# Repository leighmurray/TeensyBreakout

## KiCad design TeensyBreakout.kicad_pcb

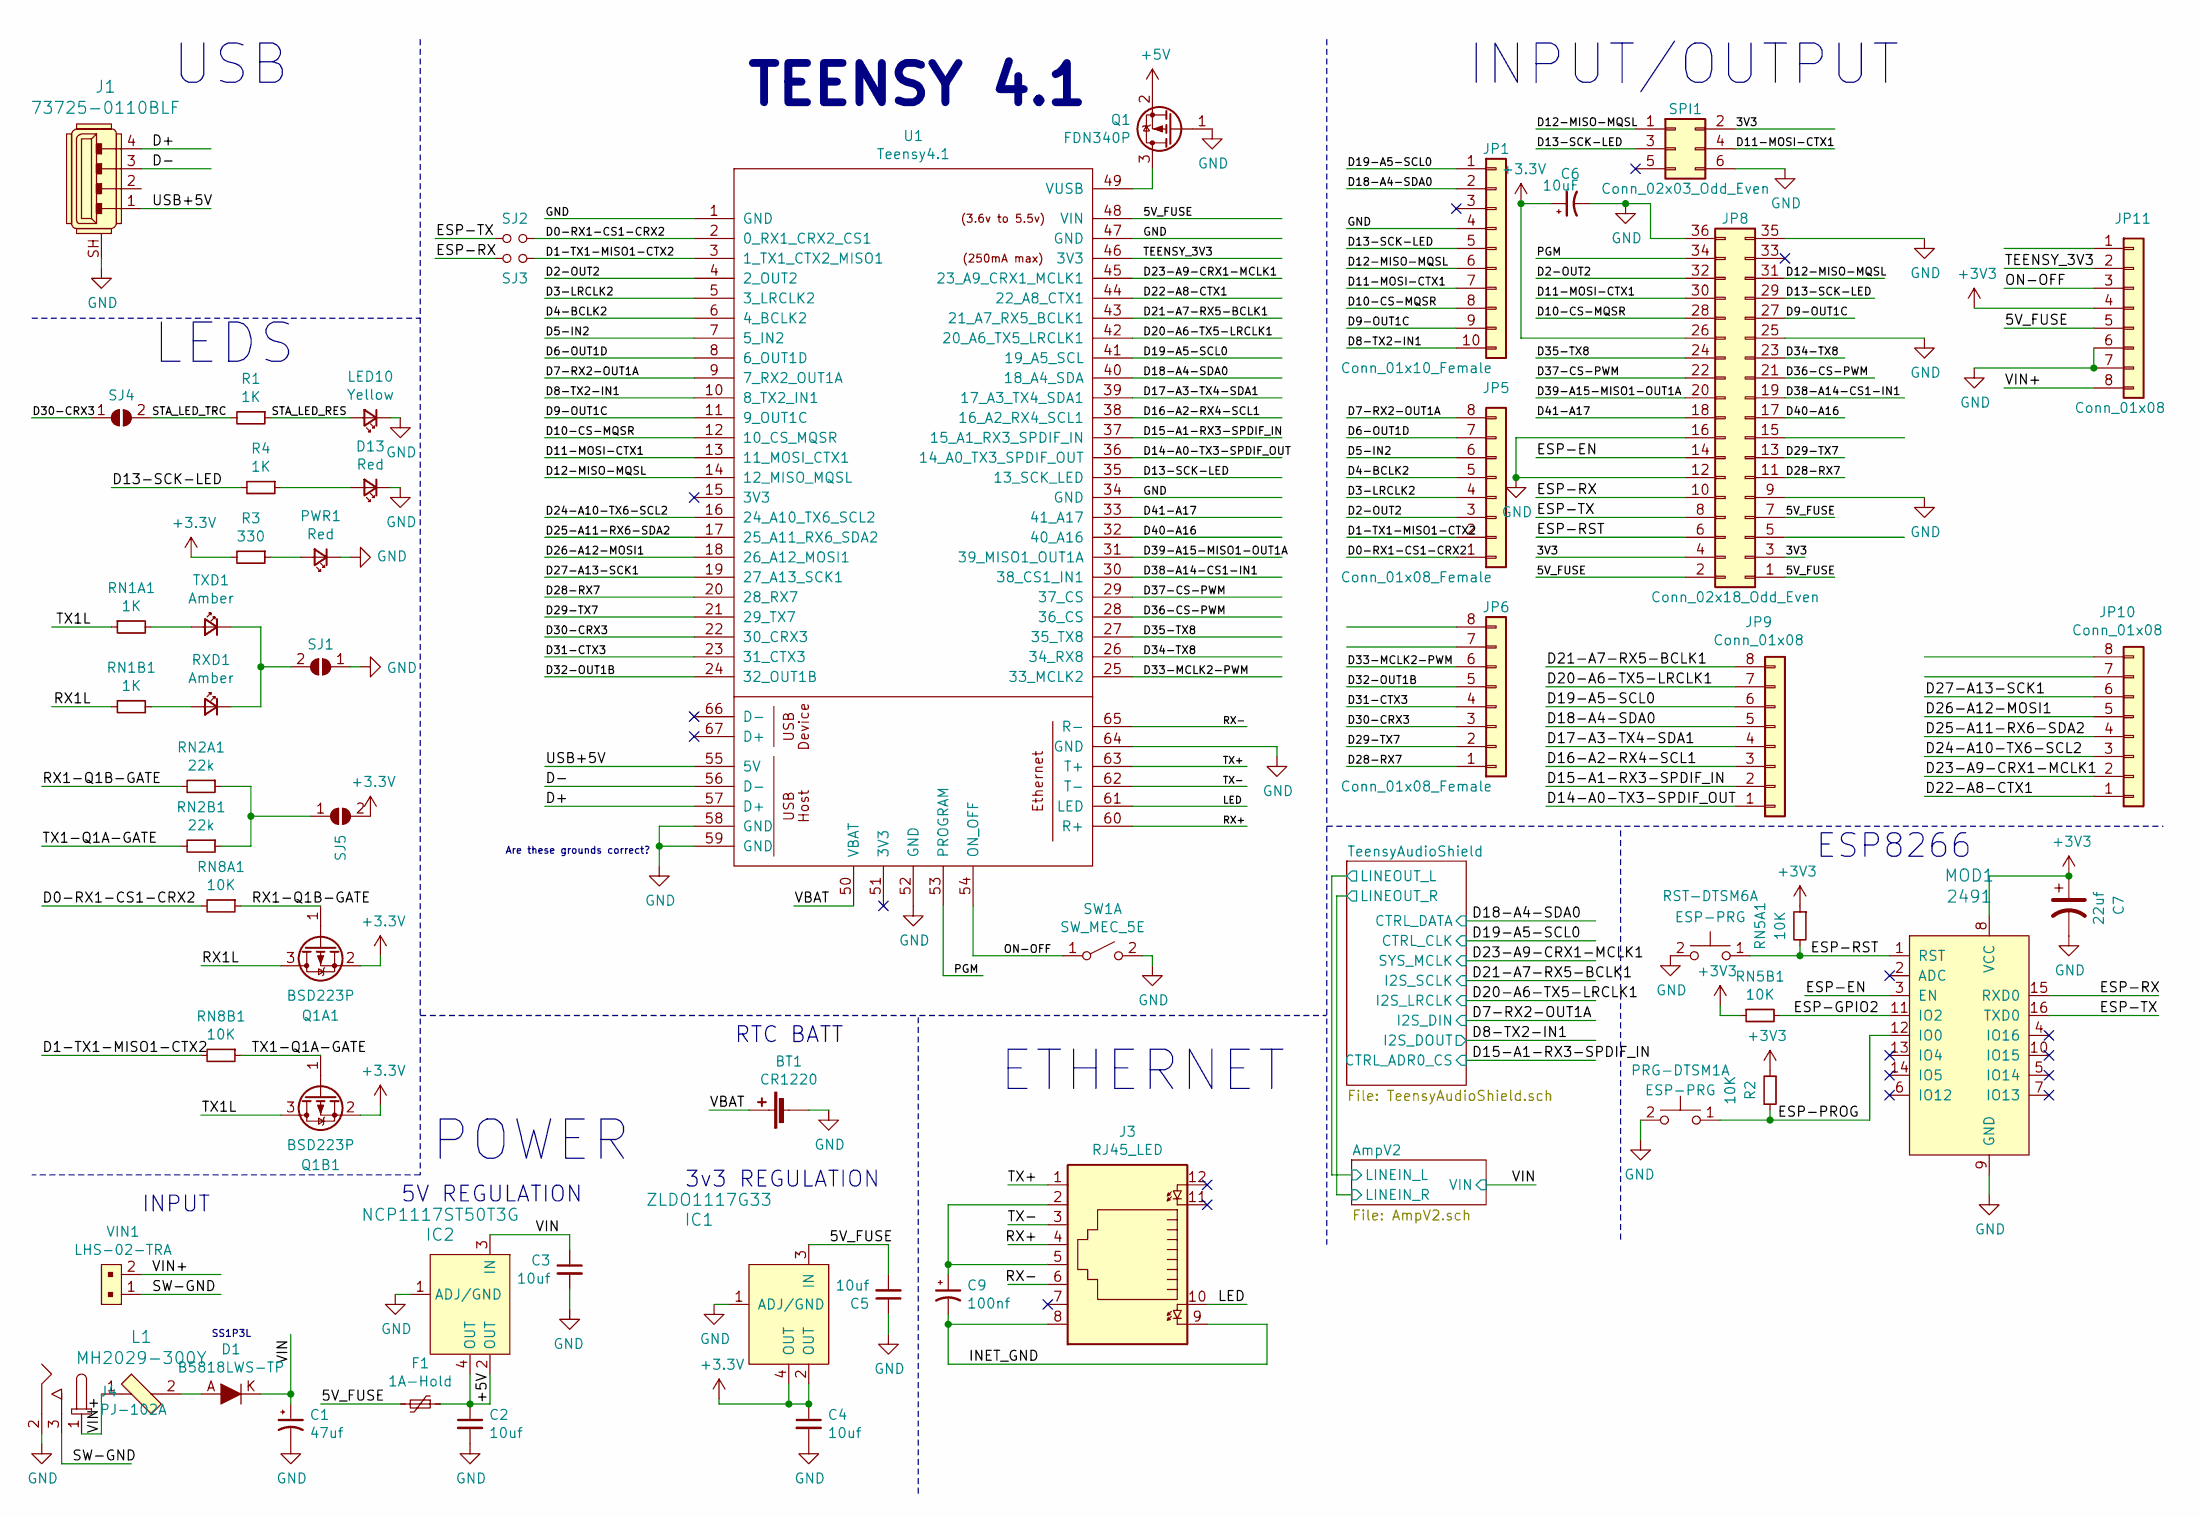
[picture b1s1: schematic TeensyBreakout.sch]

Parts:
BT1: CR1220; BatteryHolder_Keystone_3000_1x12mm
C1: 47uf; CP_Radial_D5.0mm_P2.50mm
C2, C3, C4, C5: 10uf; C_0603_1608Metric_Pad1.08x0.95mm_HandSolder
C6: 10uF; C_0603_1608Metric_Pad1.08x0.95mm_HandSolder
C7: 22uf; C_0603_1608Metric_Pad1.08x0.95mm_HandSolder
C9: 100nf; C_0603_1608Metric_Pad1.08x0.95mm_HandSolder
D1: B5818LWS-TP; SOD-323
D13: Red; LED_0603_1608Metric_Pad1.05x0.95mm_HandSolder
F1: 1A-Hold; Fuse_0603_1608Metric_Pad1.05x0.95mm_HandSolder
IC1: ZLDO1117G33; SOT-223; MPN NCP1117ST33T3G; Digi-Key_PN NCP1117ST33T3GOSCT-ND
IC2: NCP1117ST50T3G; SOT-223; MPN NCP1117ST50T3G; Digi-Key_PN NCP1117ST50T3GOSCT-ND
J1: 73725-0110BLF; USB_A_Female_Vertical_RA_73725-0110BLF; MPN 73725-0110BLF; Digi-Key_PN 609-1041-ND
J3: RJ45_LED; RJ45_Amphenol_RJHSE538X
J4: PJ-102A; Barrel_Jack_5.5mmODx2.1mmID_PJ-102A; MPN PJ-102A; Digi-Key_PN CP-102A-ND
JP1: Conn_01x10_Female; PinSocket_1x10_P2.54mm_Vertical
JP5, JP6: Conn_01x08_Female; PinSocket_1x08_P2.54mm_Vertical
JP8: Conn_02x18_Odd_Even; PinSocket_2x18_P2.54mm_VerticalFlipped
JP9, JP10, JP11: Conn_01x08; PinSocket_1x08_P2.54mm_Vertical
L1: MH2029-300Y; R_0603_1608Metric_Pad0.98x0.95mm_HandSolder; MPN BLM18PG121SN1D; Digi-Key_PN 490-1037-1-ND
LED10: Yellow; LED_0603_1608Metric_Pad1.05x0.95mm_HandSolder
MOD1: 2491; WIFI_Module_ESP8266_2491; MPN 2491; Digi-Key_PN 1528-1438-ND
PRG-DTSM1: ESP-PRG; SW_PUSH_6mm
PWR1: Red; LED_0603_1608Metric_Pad1.05x0.95mm_HandSolder
Q1: FDN340P; SOT-23
Q1A1, Q1B1: BSD223P; SOT-23
R1, R4: 1K; R_0603_1608Metric_Pad0.98x0.95mm_HandSolder
R2: 10K; R_0603_1608Metric_Pad0.98x0.95mm_HandSolder
R3: 330; R_0603_1608Metric_Pad0.98x0.95mm_HandSolder
RN1A1, RN1B1: 1K; R_0603_1608Metric_Pad0.98x0.95mm_HandSolder
RN2A1, RN2B1: 22k; R_0603_1608Metric_Pad0.98x0.95mm_HandSolder
RN5A1, RN5B1, RN8A1, RN8B1: 10K; R_0603_1608Metric_Pad0.98x0.95mm_HandSolder
RST-DTSM6: ESP-PRG; SW_PUSH_6mm
RXD1: Amber; LED_0603_1608Metric_Pad1.05x0.95mm_HandSolder
SJ1, SJ4, SJ5: SolderJumper_2_Open; SolderJumper-2_P1.3mm_Open_TrianglePad1.0x1.5mm
SJ2, SJ3: Jumper_NO_Small; PinHeader_1x02_P2.54mm_Vertical
SPI1: Conn_02x03_Odd_Even; PinSocket_2x03_P2.54mm_Vertical(Flipped)
SW1: SW_MEC_5E; SW_PUSH_6mm
TXD1: Amber; LED_0603_1608Metric_Pad1.05x0.95mm_HandSolder
U1: Teensy4.1; Teensy41
VIN1: LHS-02-TRA; JST_PH_S2B-PH-K_1x02_P2.00mm_Horizontal; MPN M20-9990246; Digi-Key_PN 952-2262-ND

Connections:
+5V: C2.1, F1.1, IC2.2 (OUT), IC2.4 (OUT), Q1.2 (S)
/3V3: JP8.3, JP8.4, SPI1.2
/5V_FUSE: C5.2, F1.2, IC1.3 (IN), JP8.1, JP8.2, JP8.7, JP11.5, U1.48 (VIN)
/D0-RX1-CS1-CRX2: JP5.1, RN8A1.2, SJ2.2, U1.2 (0_RX1_CRX2_CS1)
/D1-TX1-MISO1-CTX2: JP5.2, RN8B1.2, SJ3.2, U1.3 (1_TX1_CTX2_MISO1)
/D2-OUT2: JP5.3, JP8.32, U1.4 (2_OUT2)
/D3-LRCLK2: JP5.4, U1.5 (3_LRCLK2)
/D4-BCLK2: JP5.5, U1.6 (4_BCLK2)
/D5-IN2: JP5.6, U1.7 (5_IN2)
/D6-OUT1D: JP5.7, U1.8 (6_OUT1D)
/D7-RX2-OUT1A: JP5.8, U1.9 (7_RX2_OUT1A); also elsewhere on the board
/D8-TX2-IN1: JP1.10, U1.10 (8_TX2_IN1); also elsewhere on the board
/D9-OUT1C: JP1.9, JP8.27, U1.11 (9_OUT1C)
/D10-CS-MQSR: JP1.8, JP8.28, U1.12 (10_CS_MQSR)
/D11-MOSI-CTX1: JP1.7, JP8.30, SPI1.4, U1.13 (11_MOSI_CTX1)
/D12-MISO-MQSL: JP1.6, JP8.31, SPI1.1, U1.14 (12_MISO_MQSL)
/D13-SCK-LED: JP1.5, JP8.29, R4.2, SPI1.3, U1.35 (13_SCK_LED)
/D14-A0-TX3-SPDIF_OUT: JP9.1, U1.36 (14_A0_TX3_SPDIF_OUT)
/D15-A1-RX3-SPDIF_IN: JP9.2, U1.37 (15_A1_RX3_SPDIF_IN); also elsewhere on the board
/D16-A2-RX4-SCL1: JP9.3, U1.38 (16_A2_RX4_SCL1)
/D17-A3-TX4-SDA1: JP9.4, U1.39 (17_A3_TX4_SDA1)
/D18-A4-SDA0: JP1.2, JP9.5, U1.40 (18_A4_SDA); also elsewhere on the board
/D19-A5-SCL0: JP1.1, JP9.6, U1.41 (19_A5_SCL); also elsewhere on the board
/D20-A6-TX5-LRCLK1: JP9.7, U1.42 (20_A6_TX5_LRCLK1); also elsewhere on the board
/D21-A7-RX5-BCLK1: JP9.8, U1.43 (21_A7_RX5_BCLK1); also elsewhere on the board
/D22-A8-CTX1: JP10.1, U1.44 (22_A8_CTX1)
/D23-A9-CRX1-MCLK1: JP10.2, U1.45 (23_A9_CRX1_MCLK1); also elsewhere on the board
/D24-A10-TX6-SCL2: JP10.3, U1.16 (24_A10_TX6_SCL2)
/D25-A11-RX6-SDA2: JP10.4, U1.17 (25_A11_RX6_SDA2)
/D26-A12-MOSI1: JP10.5, U1.18 (26_A12_MOSI1)
/D27-A13-SCK1: JP10.6, U1.19 (27_A13_SCK1)
/D28-RX7: JP6.1, JP8.11, U1.20 (28_RX7)
/D29-TX7: JP6.2, JP8.13, U1.21 (29_TX7)
/D30-CRX3: JP6.3, SJ4.1 (A), U1.22 (30_CRX3)
/D31-CTX3: JP6.4, U1.23 (31_CTX3)
/D32-OUT1B: JP6.5, U1.24 (32_OUT1B)
/D33-MCLK2-PWM: JP6.6, U1.25 (33_MCLK2)
/D34-TX8: JP8.23, U1.26 (34_RX8)
/D35-TX8: JP8.24, U1.27 (35_TX8)
/D36-CS-PWM: JP8.21, U1.28 (36_CS)
/D37-CS-PWM: JP8.22, U1.29 (37_CS)
/D38-A14-CS1-IN1: JP8.19, U1.30 (38_CS1_IN1)
/D39-A15-MISO1-OUT1A: JP8.20, U1.31 (39_MISO1_OUT1A)
/D40-A16: JP8.17, U1.32 (40_A16)
/D41-A17: JP8.18, U1.33 (41_A17)
/D+: J1.4, U1.57 (D+)
/D-: J1.3, U1.56 (D-)
/ESP-EN: JP8.14, MOD1.3 (EN)
/ESP-GPIO2: MOD1.11 (IO2), RN5B1.2
/ESP-PROG: MOD1.12 (IO0), PRG-DTSM1.1 (C), R2.2
/ESP-RST: JP8.6, MOD1.1 (RST), RN5A1.2, RST-DTSM6.1 (C)
/ESP-RX: JP8.10, MOD1.15 (RXD0), SJ3.1
/ESP-TX: JP8.8, MOD1.16 (TXD0), SJ2.1
/INET_GND: C9.2, J3.8, J3.9
/LED: J3.10, U1.61 (LED)
/ON-OFF: JP11.3, SW1.1 (A), U1.54 (ON_OFF)
/PGM: JP8.34, U1.53 (PROGRAM)
/RX1-Q1B-GATE: Q1A1.1 (G), RN2A1.2, RN8A1.1
/RX1L: Q1A1.3 (D), RN1B1.1
/RX+: J3.4, U1.60 (R+)
/RX-: J3.6, U1.65 (R-)
/STA_LED_RES: LED10.2 (A), R1.1
/STA_LED_TRC: R1.2, SJ4.2 (B)
/SW-GND: J4.3, VIN1.1
/TEENSY_3V3: JP11.2, U1.46 (3V3)
/TX1-Q1A-GATE: Q1B1.1 (G), RN2B1.2, RN8B1.1
/TX1L: Q1B1.3 (D), RN1A1.1
/TX+: J3.1, U1.63 (T+)
/TX-: J3.3, U1.62 (T-)
/USB+5V: J1.1, U1.55 (5V)
/VBAT: BT1.1 (+), U1.50 (VBAT)
/VIN: C1.1, C3.1, D1.K, IC2.3 (IN); also elsewhere on the board
/VIN+: J4.1, JP11.8, L1.1, VIN1.2
GND: BT1.2 (-), C1.2, C2.2, C3.2, C4.2, C5.1, C6.2, C7.2, D13.1 (K), IC1.1 (ADJ/GND), IC2.1 (ADJ/GND), J1.SH, J4.2, JP1.4, JP8.9, JP8.12, JP8.16, JP8.25, JP8.35, JP8.36, JP11.6, JP11.7, LED10.1 (K), MOD1.9 (GND), PRG-DTSM1.2 (D), PWR1.1 (K), Q1.1 (G), RST-DTSM6.2 (D), SJ1.1 (A), SPI1.6, SW1.2 (B), U1.1 (GND), U1.34 (GND), U1.47 (GND), U1.52 (GND), U1.58 (GND), U1.59 (GND), U1.64 (GND); also elsewhere on the board
unnamed: C9.1, J3.2, J3.5
unnamed: D1.A, L1.2
unnamed: D13.2 (A), R4.1
unnamed: PWR1.2 (A), R3.1
unnamed: Q1.3 (D), U1.49 (VUSB)
unnamed: RN1A1.2, TXD1.2 (A)
unnamed: RN1B1.2, RXD1.2 (A)
unnamed: RN2A1.1, RN2B1.1, SJ5.1 (A)
unnamed: RXD1.1 (K), SJ1.2 (B), TXD1.1 (K)

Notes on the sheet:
TEENSY 4.1
INPUT/OUTPUT
USB
LEDS
POWER
3v3 REGULATION
RTC BATT
5V REGULATION
INPUT
ETHERNET
Are these grounds correct?
SS1P3L
ESP8266

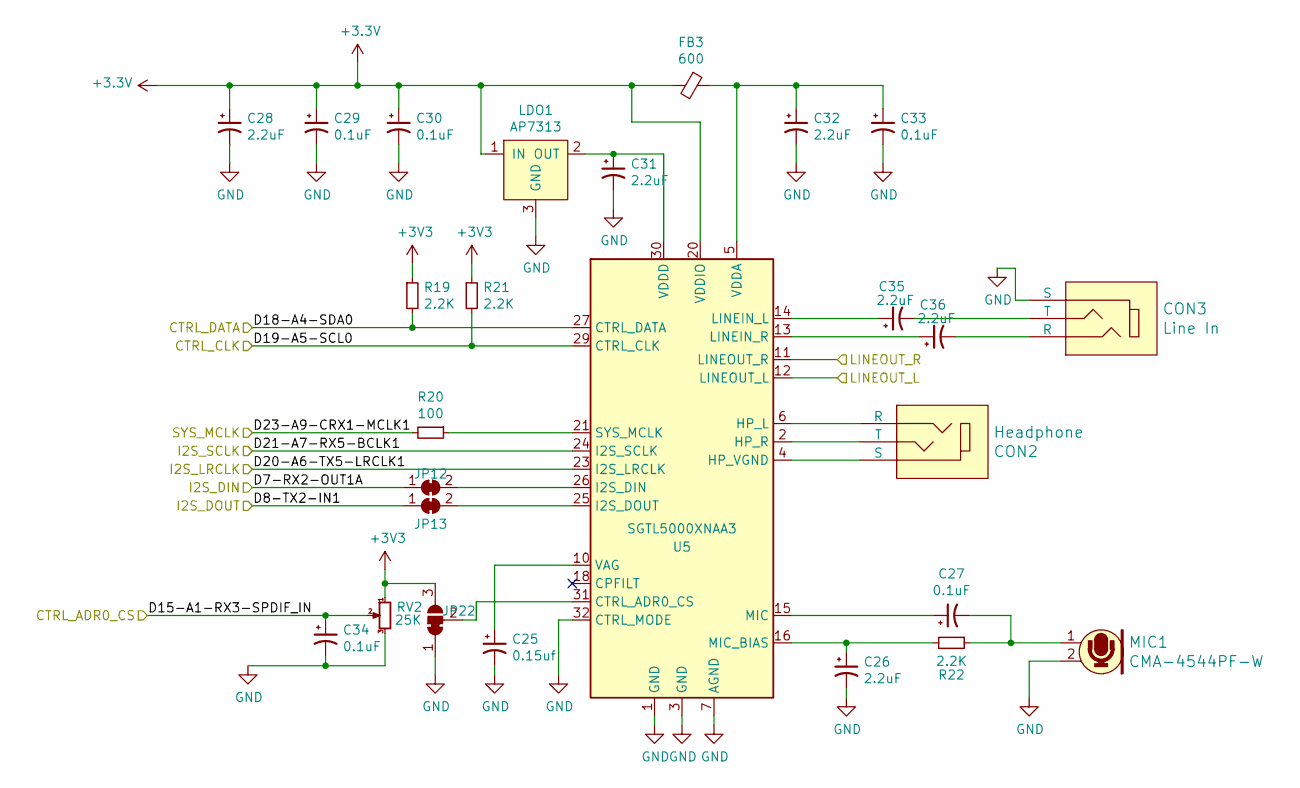
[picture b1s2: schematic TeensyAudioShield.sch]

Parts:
C25: 0.15uf; C_0603_1608Metric_Pad1.08x0.95mm_HandSolder
C26, C28, C31, C32, C35, C36: 2.2uF; C_0603_1608Metric_Pad1.08x0.95mm_HandSolder
C27, C29, C30, C33, C34: 0.1uF; C_0603_1608Metric_Pad1.08x0.95mm_HandSolder
CON2: Headphone; Switch_Slide_11.6x4mm_SJ-3523-SMT; MPN SJ-3523-SMT-TR; Digi-Key_PN CP-3523SJCT-ND
CON3: Line In; Switch_Slide_11.6x4mm_SJ-3523-SMT; MPN SJ-3523-SMT-TR; Digi-Key_PN CP-3523SJCT-ND
FB3: 600; 0805
JP12, JP13: SolderJumper_2_Bridged; SolderJumper-2_P1.3mm_Bridged_Pad1.0x1.5mm
JP22: SolderJumper_3_Bridged12; SolderJumper-3_P1.3mm_Bridged12_RoundedPad1.0x1.5mm_NumberL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
LDO1: AP7313; SOT-23_Handsoldering
MIC1: CMA-4544PF-W; Mic_CMA-4544PF-W; MPN CMA-4544PF-W; Digi-Key_PN 102-1721-ND
R19, R21, R22: 2.2K; R_0603_1608Metric_Pad0.98x0.95mm_HandSolder
R20: 100; R_0603_1608Metric_Pad0.98x0.95mm_HandSolder
RV2: 25K; Potentiometer_TT_P0915N
U5: SGTL5000XNAA3; QFN-32-1EP_5x5mm_P0.5mm_EP3.6x3.6mm

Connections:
/AmpV2/LINEIN_L: U5.12 (LINEOUT_L); also elsewhere on the board
/AmpV2/LINEIN_R: U5.11 (LINEOUT_R); also elsewhere on the board
/D7-RX2-OUT1A: JP12.1 (A); also elsewhere on the board
/D8-TX2-IN1: JP13.1 (A); also elsewhere on the board
/D15-A1-RX3-SPDIF_IN: C34.1, RV2.2; also elsewhere on the board
/D18-A4-SDA0: R19.2, U5.27 (CTRL_DATA); also elsewhere on the board
/D19-A5-SCL0: R21.2, U5.29 (CTRL_CLK); also elsewhere on the board
/D20-A6-TX5-LRCLK1: U5.23 (I2S_LRCLK); also elsewhere on the board
/D21-A7-RX5-BCLK1: U5.24 (I2S_SCLK); also elsewhere on the board
/D23-A9-CRX1-MCLK1: R20.2; also elsewhere on the board
GND: C25.2, C26.2, C28.2, C29.2, C30.2, C31.2, C32.2, C33.2, C34.2, CON3.1 (S), JP22.1 (A), LDO1.3 (GND), MIC1.2, RV2.3, U5.1 (GND), U5.3 (GND), U5.7 (AGND), U5.32 (CTRL_MODE); also elsewhere on the board
unnamed: C25.1, U5.10 (VAG)
unnamed: C26.1, R22.2, U5.16 (MIC_BIAS)
unnamed: C27.1, U5.15 (MIC)
unnamed: C27.2, MIC1.1, R22.1
unnamed: C31.1, LDO1.2 (OUT), U5.30 (VDDD)
unnamed: C32.1, C33.1, FB3.1, U5.5 (VDDA)
unnamed: C35.1, U5.14 (LINEIN_L)
unnamed: C35.2, CON3.2 (T)
unnamed: C36.1, U5.13 (LINEIN_R)
unnamed: C36.2, CON3.3 (R)
unnamed: CON2.1 (S), U5.4 (HP_VGND)
unnamed: CON2.2 (T), U5.2 (HP_R)
unnamed: CON2.3 (R), U5.6 (HP_L)
unnamed: JP12.2 (B), U5.26 (I2S_DIN)
unnamed: JP13.2 (B), U5.25 (I2S_DOUT)
unnamed: JP22.2 (C), U5.31 (CTRL_ADR0_CS)
unnamed: R20.1, U5.21 (SYS_MCLK)

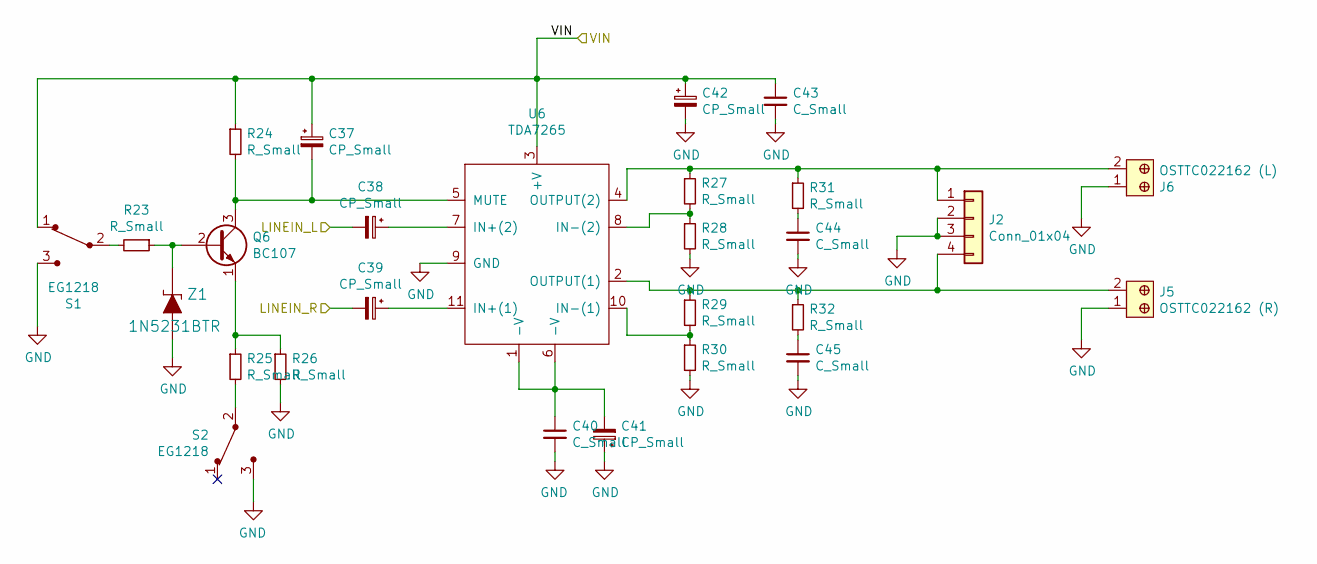
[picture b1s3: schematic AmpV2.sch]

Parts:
C37, C38, C39, C41, C42: CP_Small; C_0603_1608Metric_Pad1.08x0.95mm_HandSolder
C40, C43, C44, C45: C_Small; C_0603_1608Metric_Pad1.08x0.95mm_HandSolder
J2: Conn_01x04; JST_PH_S4B-PH-K_1x04_P2.00mm_Horizontal
J5: OSTTC022162 (R); Term_Block_1x2_P5.08MM; MPN OSTTC022162; Digi-Key_PN ED2609-ND
J6: OSTTC022162 (L); Term_Block_1x2_P5.08MM; MPN OSTTC022162; Digi-Key_PN ED2609-ND
Q6: BC107; TO-18-3
R23, R24, R25, R26, R27, R28, R29, R30, R31, R32: R_Small; R_0603_1608Metric_Pad0.98x0.95mm_HandSolder
S1, S2: EG1218; Switch_Slide_JS202011SCQN; MPN EG1218; Digi-Key_PN EG1903-ND
U6: TDA7265; TO-220-11_P3.4x5.08mm_StaggerOdd_Lead4.85mm_Vertical
Z1: 1N5231BTR; DO-35; MPN 1N5231BTR; Digi-Key_PN 1N5231BFSCT-ND

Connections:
/AmpV2/LINEIN_L: C38.2; also elsewhere on the board
/AmpV2/LINEIN_R: C39.2; also elsewhere on the board
/VIN: C37.1, C42.1, C43.1, R24.1, S1.1, U6.3 (+V); also elsewhere on the board
GND: C40.2, C41.1, C42.2, C43.2, C44.2, C45.2, J2.2, J2.3, J5.1, J6.1, R26.2, R28.2, R30.2, S1.3, S2.3, U6.9 (GND), Z1.A; also elsewhere on the board
unnamed: C37.2, Q6.3 (C), R24.2, U6.5 (MUTE)
unnamed: C38.1, U6.7 (IN+(2))
unnamed: C39.1, U6.11 (IN+(1))
unnamed: C40.1, C41.2, U6.1 (-V), U6.6 (-V)
unnamed: C44.1, R31.2
unnamed: C45.1, R32.2
unnamed: J2.1, J6.2, R27.1, R31.1, U6.4 (OUTPUT(2))
unnamed: J2.4, J5.2, R29.1, R32.1, U6.2 (OUTPUT(1))
unnamed: Q6.1 (E), R25.1, R26.1
unnamed: Q6.2 (B), R23.1, Z1.K
unnamed: R23.2, S1.2
unnamed: R25.2, S2.2
unnamed: R27.2, R28.1, U6.8 (IN-(2))
unnamed: R29.2, R30.1, U6.10 (IN-(1))

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
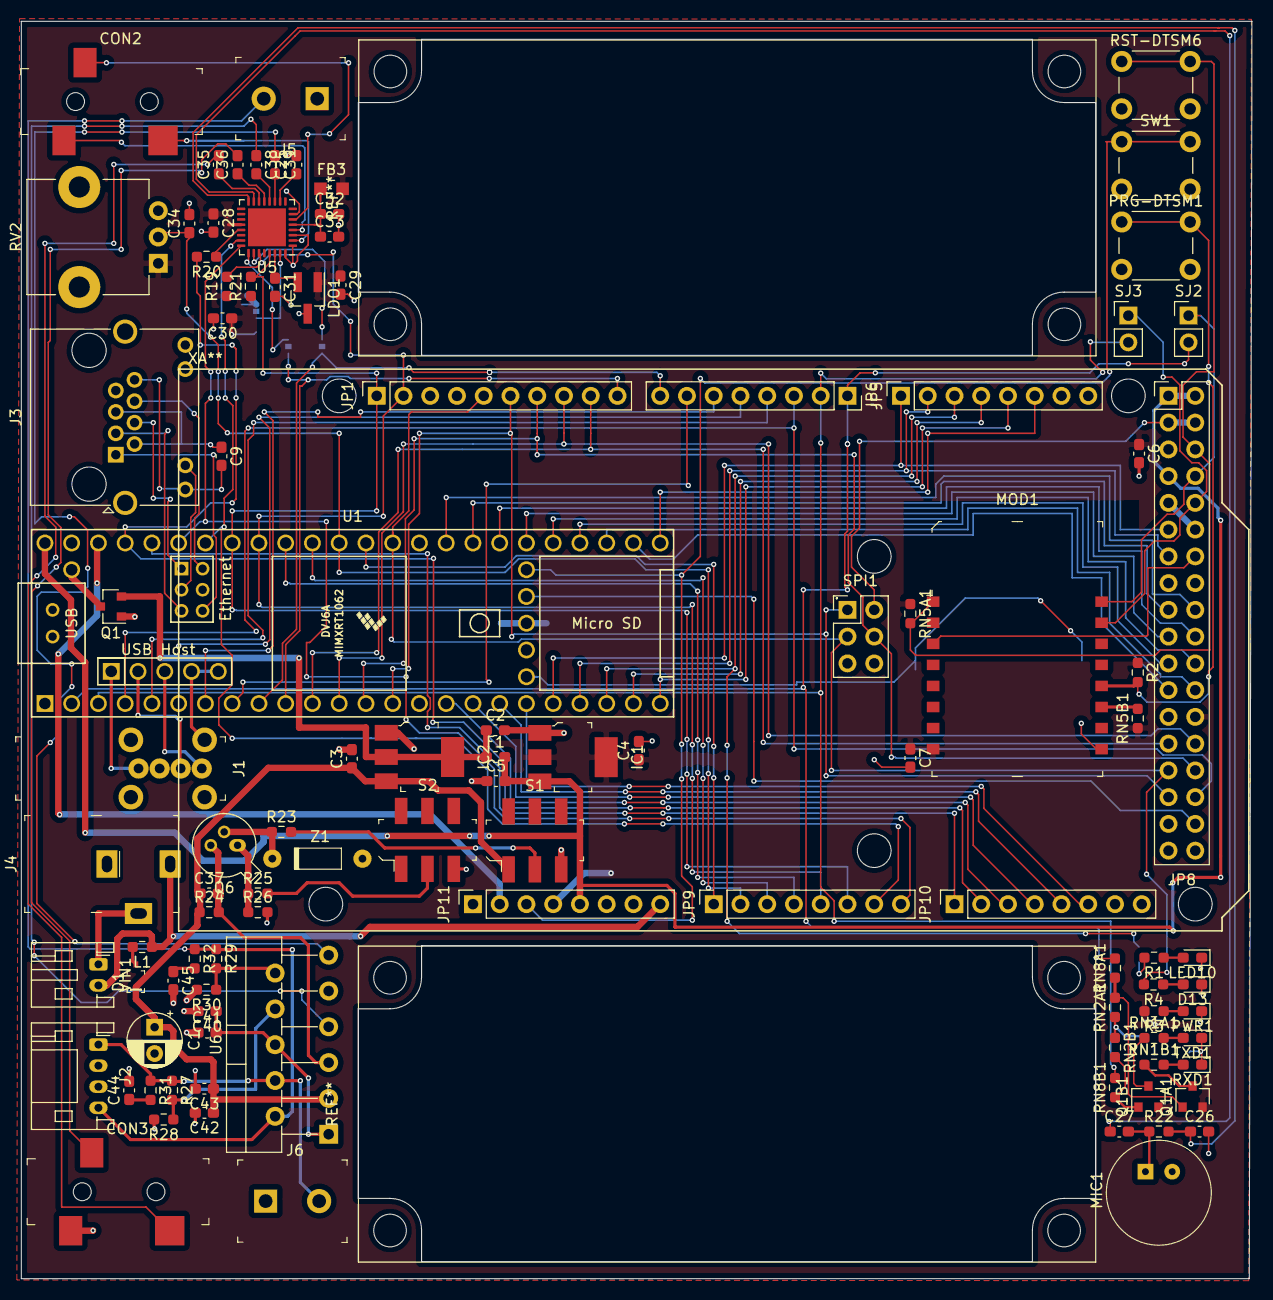
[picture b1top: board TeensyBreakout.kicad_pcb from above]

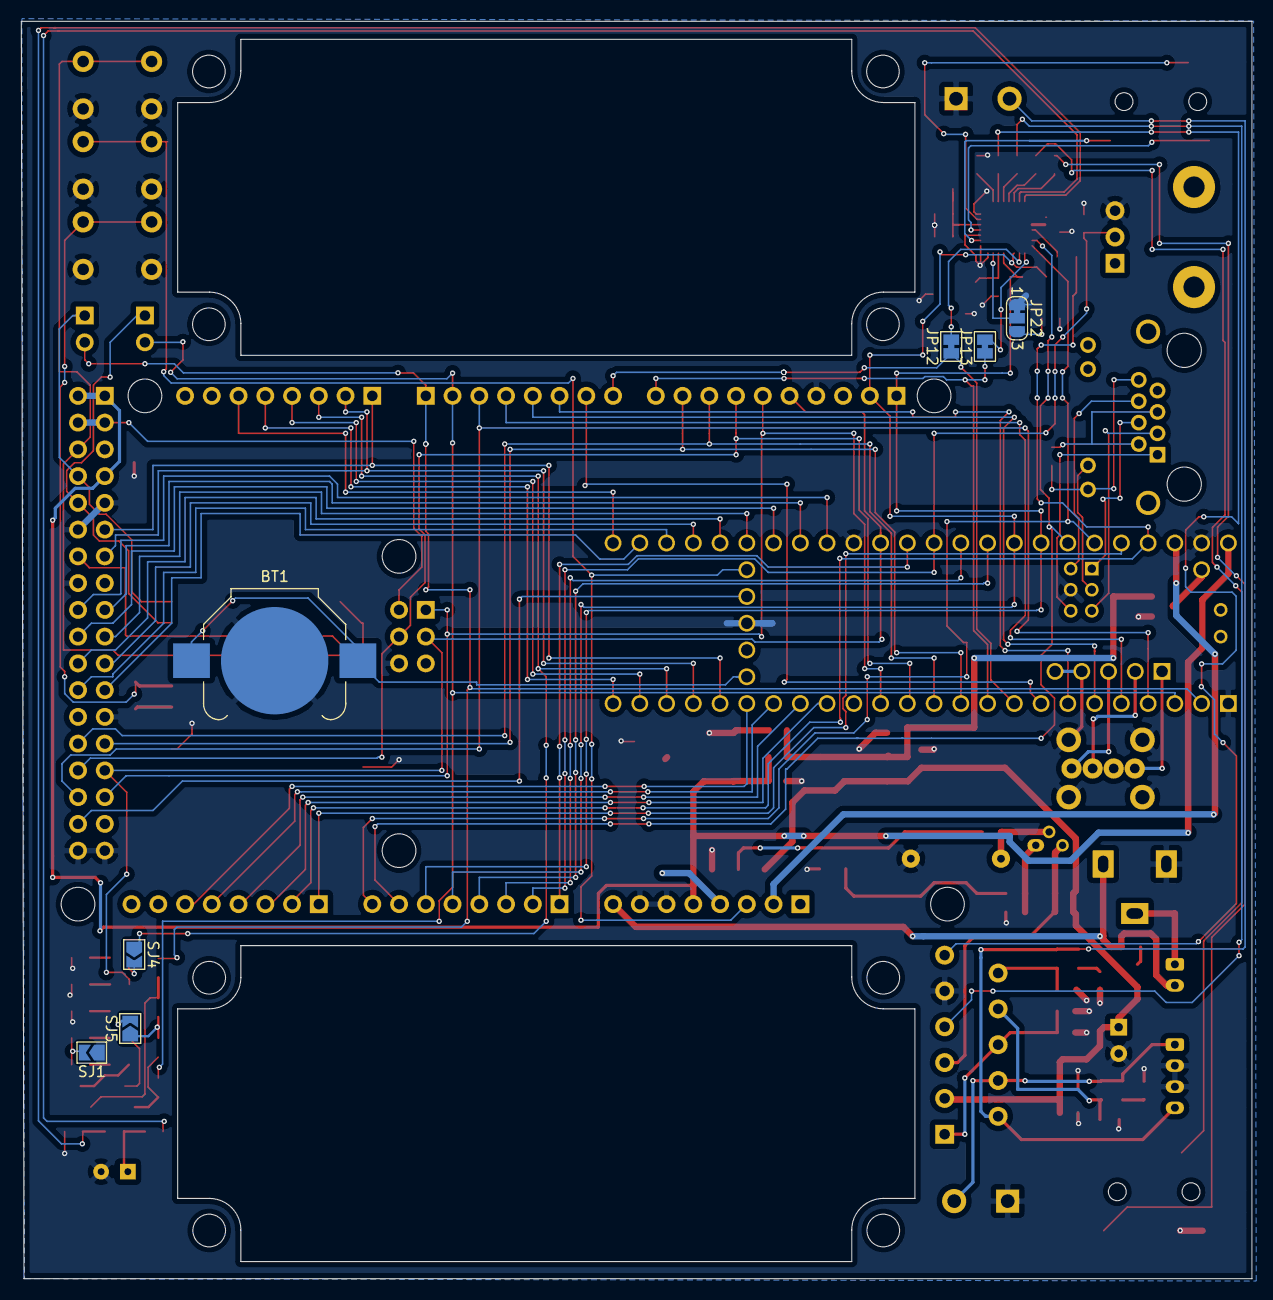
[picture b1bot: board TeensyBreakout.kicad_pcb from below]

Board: 2 copper layers, 116.8 x 119.4 mm, 110 parts (7 on the bottom side), 117 nets.

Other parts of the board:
XA**: Arduino_Due_Shield

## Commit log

2021-12-06 all components added, need to check and create one power source
2021-12-09 removing old amp, can't buy chip
2021-12-10 making layout
2021-12-10 added speaker cutouts
2021-12-13 before downsizing
2021-12-14 gonna try auto-route
2021-12-19 svgs exported
2021-12-20 added pdf schematic
2021-12-25 redoing traces
2021-12-25 the back ports are wrong, need to rotate
2021-12-25 made more room for speakers and corrected rotation of furthest headers
2021-12-28 lots of wires left
2021-12-29 progress
2021-12-29 finished traces
2022-01-06 moved media files
2022-01-06 moved pdf back because i linked to it
